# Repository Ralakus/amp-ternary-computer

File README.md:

## Members

Mikhail Schneide, Computer Science Student (2026)
mkl@vt.edu

## Mentor

MENTOR NAME HERE

## Current Status

IN PROGRESS

## Project Overview

The project aims to build a simple 6-trit ternary computer using CMOS gates. The basic ternary gates using CMOS logic but a full open-source computer built from these gates has not been done yet. The computer will support 12-trit addressing to allow 531441 trytes of address space. 

I've already built out the basic gates and tested them using a multimeter, Tektronix 2245A, and Meanwell RT-50A power supply. I had some prototypes throughout the years of the components but never had the funding to fully built out a computer.

## Educational Value Added

Balanced ternary computing is not studied by many computer engineers or computer scientists. Building a simple balanced ternary computer would allow students study balanced ternary computing and mathematics.

## Tasks

<!-- Your Text Here. You may work with your mentor on this later when they are assigned -->

1. Clean up the current repository
2. Validate all of the gates with an oscilloscope to ensure they match the ngspice simulations
3. Create the ISA for the computer
4. Create the block diagram for the computer
5. Fill in the schematics for each block of the computer
6. Order bulk panels of each gate
7. Assemble computer on top of proto-board

## Design Decisions

<!-- Your Text Here. You may work with your mentor on this later when they are assigned -->
6-trits was chosen to balance cost and usability. Older CPUs has 8-bit architectures with 16-bit addressing. A 6-trit architecture with 12-bit addressing helps balance out the cost, complexity, and capability. 

## Design Misc

<!-- Your Text Here. You may work with your mentor on this later when they are assigned -->

## Steps for Documenting Your Design Process

<!-- Your Text Here. You may work with your mentor on this later when they are assigned -->

## BOM + Component Cost

<!-- Your Text Here. You may work with your mentor on this later when they are assigned -->

## Timeline

<!-- Your Text Here. You may work with your mentor on this later when they are assigned -->

## Useful Links

<!-- Your Text Here. You may work with your mentor on this later when they are assigned -->

* Ternary logic and assembly resources: [https://licas.tech/tritium_resources/](https://licas.tech/tritium_resources/)

## Log

<!-- Your Text Here. You may work with your mentor on this later when they are assigned -->
* 3/31/2025 - Migrated from personal repo into AMP-Lab project repository

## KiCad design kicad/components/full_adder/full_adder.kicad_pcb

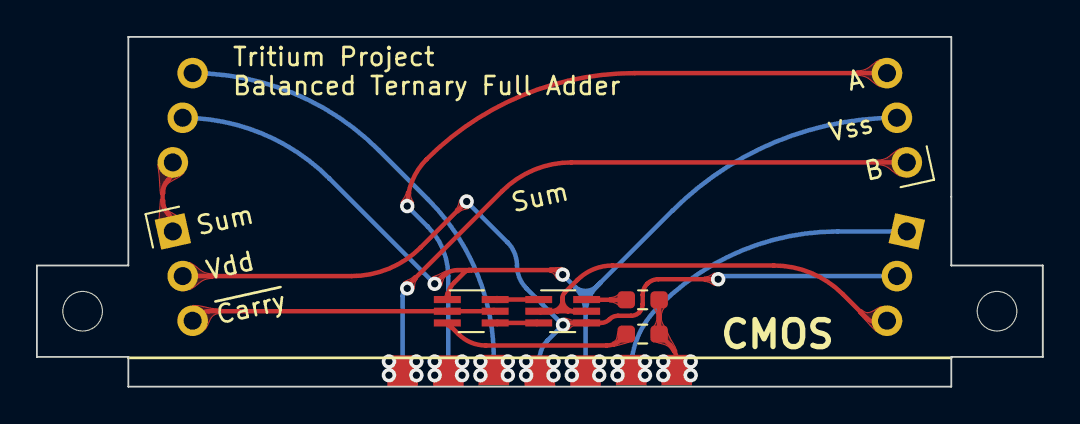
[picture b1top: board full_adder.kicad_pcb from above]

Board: 2 copper layers, 55.9 x 19.4 mm, 6 parts (1 on the bottom side), 10 nets.

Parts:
Q1, Q2: BSS8402DW-7-F; SOT-363_SC-70-6_Handsoldering
R1, R2: 12k; R_0603_1608Metric_Pad0.98x0.95mm_HandSolder
U1, U2: Sum

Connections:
/NAny/A: Q1.2 (G), Q1.5 (G), U2.3 (~Carry)
/NAny/B: Q2.2 (G), Q2.5 (G), U1.3 (~Carry)
Carry: R1.2, R2.1
unnamed: Q1.1 (S), Q2.6 (D)
unnamed: Q1.3 (D), Q2.4 (S)
unnamed: Q1.6 (D), R2.2
unnamed: Q2.3 (D), R1.1
unnamed: U1.1 (Sum), U2.6 (B)
VDD: Q1.4 (S), U1.2 (Vdd), U2.2 (Vdd)
VSS: Q2.1 (S), U1.5 (Vss), U2.5 (Vss)

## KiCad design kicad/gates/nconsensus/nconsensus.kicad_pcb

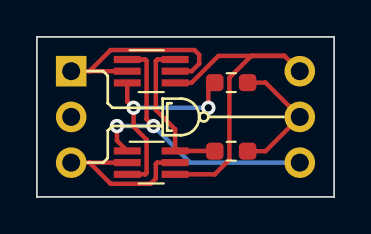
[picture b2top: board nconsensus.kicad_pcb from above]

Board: 2 copper layers, 16.5 x 8.9 mm, 6 parts (0 on the bottom side), 7 nets.

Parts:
J1, J2: Conn_01x03; PinHeader_1x03_P2.54mm_Vertical_NoSilkscreen
Q1, Q2: BSS8402DW-7-F; SOT-363_SC-70-6_Handsoldering
R1, R2: 12k; R_0603_1608Metric_Pad0.98x0.95mm_HandSolder

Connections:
A: J1.3, Q2.2 (G), Q2.5 (G)
B: J1.1, Q1.2 (G), Q1.5 (G)
unnamed: Q1.3 (D), Q2.3 (D), R1.1
unnamed: Q1.6 (D), Q2.6 (D), R2.2
Out: J2.2, R1.2, R2.1
VDD: J2.1, Q1.4 (S), Q2.4 (S)
VSS: J2.3, Q1.1 (S), Q2.1 (S)

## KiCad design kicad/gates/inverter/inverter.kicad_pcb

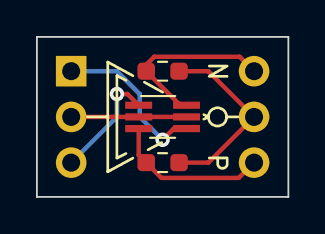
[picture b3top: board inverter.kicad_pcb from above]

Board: 2 copper layers, 14.0 x 8.9 mm, 5 parts (0 on the bottom side), 6 nets.

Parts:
J1, J2: Conn_01x03; PinHeader_1x03_P2.54mm_Vertical_NoSilkscreen
Q1: BSS8402DW-7-F; SOT-363_SC-70-6_Handsoldering
R1, R2: 12k; R_0603_1608Metric_Pad0.98x0.95mm_HandSolder

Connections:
In: J1.2, Q1.2 (G), Q1.5 (G)
Nti: J2.1, Q1.6 (D), R2.2
Out: J2.2, R1.2, R2.1
Pti: J2.3, Q1.3 (D), R1.1
VDD: J1.1, Q1.4 (S)
VSS: J1.3, Q1.1 (S)

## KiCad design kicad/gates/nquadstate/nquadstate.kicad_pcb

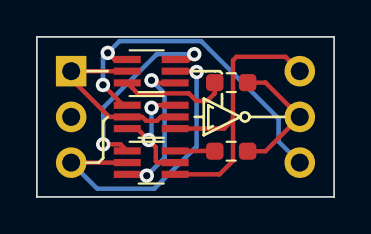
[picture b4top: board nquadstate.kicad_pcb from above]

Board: 2 copper layers, 16.5 x 8.9 mm, 7 parts (0 on the bottom side), 10 nets.

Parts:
J1, J2: Conn_01x03; PinHeader_1x03_P2.54mm_Vertical_NoSilkscreen
Q1, Q2, Q3: BSS8402DW-7-F; SOT-363_SC-70-6_Handsoldering
R1, R2: 12k; R_0603_1608Metric_Pad0.98x0.95mm_HandSolder

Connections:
Gate: J1.1, Q1.2 (G), Q1.5 (G), Q3.2 (G)
In: J1.3, Q2.2 (G), Q3.5 (G)
unnamed: Q1.3 (D), Q1.6 (D), Q2.5 (G)
unnamed: Q2.1 (S), Q3.6 (D)
unnamed: Q2.3 (D), Q3.4 (S)
unnamed: Q2.6 (D), R2.2
unnamed: Q3.3 (D), R1.1
Out: J2.2, R1.2, R2.1
VDD: J2.1, Q1.4 (S), Q2.4 (S)
VSS: J2.3, Q1.1 (S), Q3.1 (S)

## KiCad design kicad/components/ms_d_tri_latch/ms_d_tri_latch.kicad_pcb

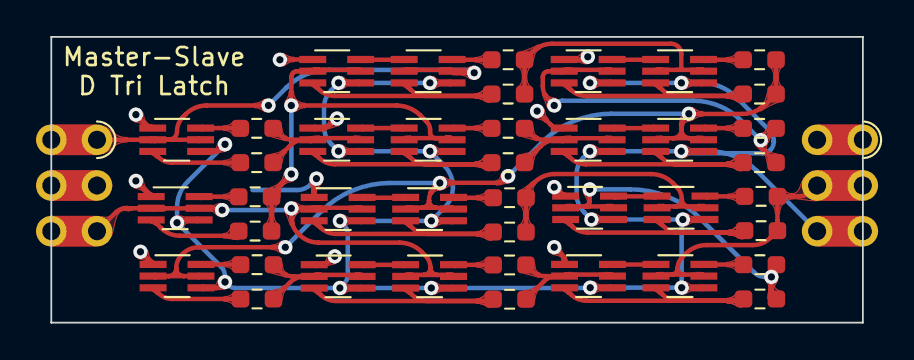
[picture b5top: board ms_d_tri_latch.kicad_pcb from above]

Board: 2 copper layers, 45.1 x 15.9 mm, 43 parts (0 on the bottom side), 45 nets.

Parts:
J1, J2: Conn_01x03; Hybrid_Castellation_1x03_P2.54
Q1, Q2, Q3, Q4, Q5, Q6, Q7, Q8, Q9, Q10, Q11, Q12, Q13, Q14, Q15, Q16, Q17, Q18, Q19: BSS8402DW-7-F; SOT-363_SC-70-6_Handsoldering
R1, R2, R3, R4, R5, R6, R7, R8, R9, R10, R11, R12, R13, R14, R15, R16, R17, R18, R19, R20, R21, R22: 12k; R_0603_1608Metric_Pad0.98x0.95mm_HandSolder

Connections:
/Inverter2/Nti: Q19.6 (D), R22.2
/Inverter2/Out: Q14.2 (G), Q14.5 (G), Q15.2 (G), Q15.5 (G), R21.2, R22.1
/Inverter2/Pti: Q19.3 (D), R21.1
/d_latch1/Antimin4/B: Q3.2 (G), Q3.5 (G), R19.2, R20.1
/d_latch1/Antimin5/Out: Q4.2 (G), Q4.5 (G), R7.2, R8.1
/d_latch1/Antimin7/B: Q18.2 (G), Q18.5 (G), R1.2, R2.1
/d_latch1/Inverter1/Nti: Q1.6 (D), R2.2
/d_latch1/Inverter1/Pti: Q1.3 (D), R1.1
/d_latch1/~Q: Q5.2 (G), Q5.5 (G), R3.2, R4.1
/d_latch/Antimin4/B: Q10.2 (G), Q10.5 (G), R17.2, R18.1
/d_latch/Antimin5/Out: Q11.2 (G), Q11.5 (G), R15.2, R16.1
/d_latch/Antimin7/B: Q16.2 (G), Q16.5 (G), R9.2, R10.1
/d_latch/Inverter1/Nti: Q8.6 (D), R10.2
/d_latch/Inverter1/Pti: Q8.3 (D), R9.1
/d_latch/Q: Q1.2 (G), Q1.5 (G), Q6.2 (G), Q6.5 (G), Q9.2 (G), Q9.5 (G), R13.2, R14.1
/d_latch/~Q: Q12.2 (G), Q12.5 (G), R11.2, R12.1
D: J1.1, Q8.2 (G), Q8.5 (G), Q13.2 (G), Q13.5 (G)
Enable: J1.3, Q7.2 (G), Q7.5 (G), Q17.2 (G), Q17.5 (G), Q19.2 (G), Q19.5 (G)
unnamed: Q2.1 (S), Q3.6 (D)
unnamed: Q2.3 (D), Q3.3 (D), R3.1
unnamed: Q2.6 (D), R4.2
unnamed: Q4.1 (S), Q5.6 (D)
unnamed: Q4.3 (D), Q5.3 (D), R5.1
unnamed: Q4.6 (D), R6.2
unnamed: Q6.1 (S), Q7.6 (D)
unnamed: Q6.3 (D), Q7.3 (D), R7.1
unnamed: Q6.6 (D), R8.2
unnamed: Q9.6 (D), R12.2
unnamed: Q9.3 (D), Q10.3 (D), R11.1
unnamed: Q9.1 (S), Q10.6 (D)
unnamed: Q11.1 (S), Q12.6 (D)
unnamed: Q11.3 (D), Q12.3 (D), R13.1
unnamed: Q11.6 (D), R14.2
unnamed: Q13.1 (S), Q14.6 (D)
unnamed: Q13.3 (D), Q14.3 (D), R15.1
unnamed: Q13.6 (D), R16.2
unnamed: Q15.1 (S), Q16.6 (D)
unnamed: Q15.3 (D), Q16.3 (D), R17.1
unnamed: Q15.6 (D), R18.2
unnamed: Q17.1 (S), Q18.6 (D)
unnamed: Q17.3 (D), Q18.3 (D), R19.1
unnamed: Q17.6 (D), R20.2
Q: J2.2, Q2.2 (G), Q2.5 (G), R5.2, R6.1
VDD: J2.3, Q1.4 (S), Q2.4 (S), Q3.4 (S), Q4.4 (S), Q5.4 (S), Q6.4 (S), Q7.4 (S), Q8.4 (S), Q9.4 (S), Q10.4 (S), Q11.4 (S), Q12.4 (S), Q13.4 (S), Q14.4 (S), Q15.4 (S), Q16.4 (S), Q17.4 (S), Q18.4 (S), Q19.4 (S)
VSS: J1.2, J2.1, Q1.1 (S), Q3.1 (S), Q5.1 (S), Q7.1 (S), Q8.1 (S), Q10.1 (S), Q12.1 (S), Q14.1 (S), Q16.1 (S), Q18.1 (S), Q19.1 (S)

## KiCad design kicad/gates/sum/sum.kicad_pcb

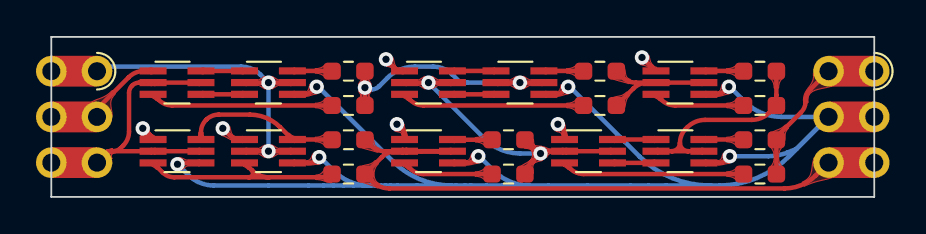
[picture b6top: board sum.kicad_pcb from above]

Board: 2 copper layers, 45.7 x 8.9 mm, 24 parts (0 on the bottom side), 28 nets.

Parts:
J1, J2: Conn_01x03; Hybrid_Castellation_1x03_P2.54
Q1, Q2, Q3, Q4, Q5, Q6, Q7, Q8, Q9, Q10: BSS8402DW-7-F; SOT-363_SC-70-6_Handsoldering
R1, R2, R3, R4, R5, R6, R7, R8, R9, R10, R11, R12: 12k; R_0603_1608Metric_Pad0.98x0.95mm_HandSolder

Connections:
/Inverter BL/Nti: Q8.6 (D), R10.2
/Inverter BL/Out: Q4.2 (G), Q4.5 (G), Q6.2 (G), Q6.5 (G), R9.2, R10.1
/Inverter BL/Pti: Q8.3 (D), R9.1
/Inverter M/In: Q7.2 (G), Q7.5 (G), R3.2, R4.1
/Inverter M/Nti: Q7.6 (D), R8.2
/Inverter M/Out: Q5.2 (G), Q5.5 (G), R7.2, R8.1
/Inverter M/Pti: Q7.3 (D), R7.1
/NAny M/A: Q3.2 (G), Q3.5 (G), R1.2, R2.1
A: J1.1, Q1.2 (G), Q1.5 (G), Q9.2 (G), Q9.5 (G)
B: J1.3, Q2.2 (G), Q2.5 (G), Q10.2 (G), Q10.5 (G)
unnamed: Q1.1 (S), Q2.6 (D)
unnamed: Q1.3 (D), Q2.4 (S)
unnamed: Q1.6 (D), R2.2
unnamed: Q2.3 (D), R1.1
unnamed: Q3.1 (S), Q4.6 (D)
unnamed: Q3.3 (D), Q4.4 (S)
unnamed: Q3.6 (D), R4.2
unnamed: Q4.3 (D), R3.1
unnamed: Q5.1 (S), Q6.6 (D)
unnamed: Q5.3 (D), Q6.4 (S)
unnamed: Q5.6 (D), R6.2
unnamed: Q6.3 (D), R5.1
unnamed: Q9.3 (D), Q10.3 (D), R11.1
unnamed: Q9.6 (D), Q10.6 (D), R12.2
Sum: J2.1, R5.2, R6.1
VDD: J2.2, Q1.4 (S), Q3.4 (S), Q5.4 (S), Q7.4 (S), Q8.4 (S), Q9.4 (S), Q10.4 (S)
VSS: J1.2, Q2.1 (S), Q4.1 (S), Q6.1 (S), Q7.1 (S), Q8.1 (S), Q9.1 (S), Q10.1 (S)
~Carry: J2.3, Q8.2 (G), Q8.5 (G), R11.2, R12.1

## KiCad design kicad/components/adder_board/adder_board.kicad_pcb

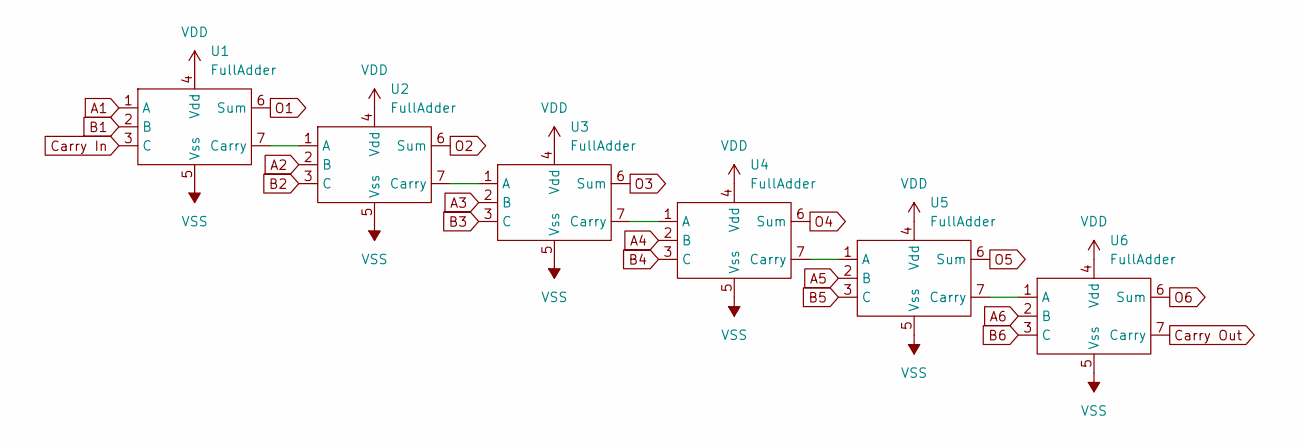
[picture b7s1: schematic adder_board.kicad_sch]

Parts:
U1, U2, U3, U4, U5, U6: FullAdder

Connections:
A1: U1.1 (A)
A2: U2.2 (B)
A3: U3.2 (B)
A4: U4.2 (B)
A5: U5.2 (B)
A6: U6.2 (B)
B1: U1.2 (B)
B2: U2.3 (C)
B3: U3.3 (C)
B4: U4.3 (C)
B5: U5.3 (C)
B6: U6.3 (C)
Carry In: U1.3 (C)
Carry Out: U6.7 (Carry)
unnamed: U1.7 (Carry), U2.1 (A)
unnamed: U2.7 (Carry), U3.1 (A)
unnamed: U3.7 (Carry), U4.1 (A)
unnamed: U4.7 (Carry), U5.1 (A)
unnamed: U5.7 (Carry), U6.1 (A)
O1: U1.6 (Sum)
O2: U2.6 (Sum)
O3: U3.6 (Sum)
O4: U4.6 (Sum)
O5: U5.6 (Sum)
O6: U6.6 (Sum)
VDD: U1.4 (Vdd), U2.4 (Vdd), U3.4 (Vdd), U4.4 (Vdd), U5.4 (Vdd), U6.4 (Vdd)
VSS: U1.5 (Vss), U2.5 (Vss), U3.5 (Vss), U4.5 (Vss), U5.5 (Vss), U6.5 (Vss)

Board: 2 copper layers, 6 parts (0 on the bottom side), 7 nets, no tracks yet.

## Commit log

2025-04-01 updated readme with current status and started work on ISA
2025-04-01 update to kicad 9
2025-04-01 New Submodule test 2
2025-04-01 testing submodule workflow
2025-04-01 Simplifying the project
2025-04-01 Updating for better workflow
2025-04-01 final submodule test
2025-04-01 New image spec
2025-04-01 Testing submodule
2025-04-01 Workflow updates:
2025-04-01 Testing live update
2025-04-01 test' git push
2025-04-01 renamed readme.adoc to description.adoc to avoid github from defaulting to readme.adoc instead of README.md
2025-04-01 added project description
2025-04-01 Latest
